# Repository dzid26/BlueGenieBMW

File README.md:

# BlueGenie BMW <br>
Bluetooth audio for BMW with CAN-bus support for steering wheel buttons control. Supported cars should be E90, E91, E92, E93, E82, E81, (also probably 5, 7-series, maybe E46).   <br> <br>

**Features**: 
- Next / Previous - (CAN-bus) steering buttons 
- OTA over Wi-Fi (hold Volume Down and Previous Song buttons on the steering to go into Dwonload mode) <br>
- Other possibilities that you can develop:
  - autmoatically enable heated seats if ambient tempreture is low)
  - display car info on your phone, if you make an app ;)
 <br>
 <br>
 
**Hardware thingies** ([BOM](https://htmlpreview.github.io/?https://github.com/dzid26/BlueGenieBMW/blob/master/Hardware/bom.html)): 
- ESP8266 - (Wemos D1 mini) ($3) (they usually come with the black sockets)  
- BK3254 (BT4.1 A2DP audio) - with UART enabled firmware (the ebay ones should be ok) ($2) 
- MCP2515 board with some transciever ($2) 
- https://oshpark.com/shared_projects/qK7vXqp4 
- Audio jack PJ-320D
- (optional) resistors (2x2.2k & 2x3.3k) for level shifting for longetivity of ESP8266. You can replace them with short wire if you're on a brave side.
<br> <br>

Solder the stuff together.
 <br> <br>

Installation: <br>
- clone the repository and also run download_libraries.bat from /lib folder  :/
- Import project to https://platformio.org/platformio-ide and flash ESP8266 using USB cable (for the first time).
- Power it with 5V cigarette charger or get Wemos power shield from ebay.
- Find K-CAN ("chasis" CAN-bus) - twisted green (CAN HIGH) and orange (CAN LOW) cables behind the radio and splice it and connect to MCP2515.  <br>

Some info regarding K-CAN - it is @100kbps  <br>
- https://us.autologic.com/news/bmw-instrument-cluster-lights-and-the-k-bus-failure  <br>
- https://www.newtis.info/tisv2/a/en/e82-123d-cou/repair-manuals/61-general-vehicle-electrical-system/2EAqiv9
- For CAN messages, refer to https://github.com/dzid26/opendbc-BMW-E8x-E9x/blob/master/bmw_e9x_e8x.dbc.

<br> <br><br> <br>
Photos:

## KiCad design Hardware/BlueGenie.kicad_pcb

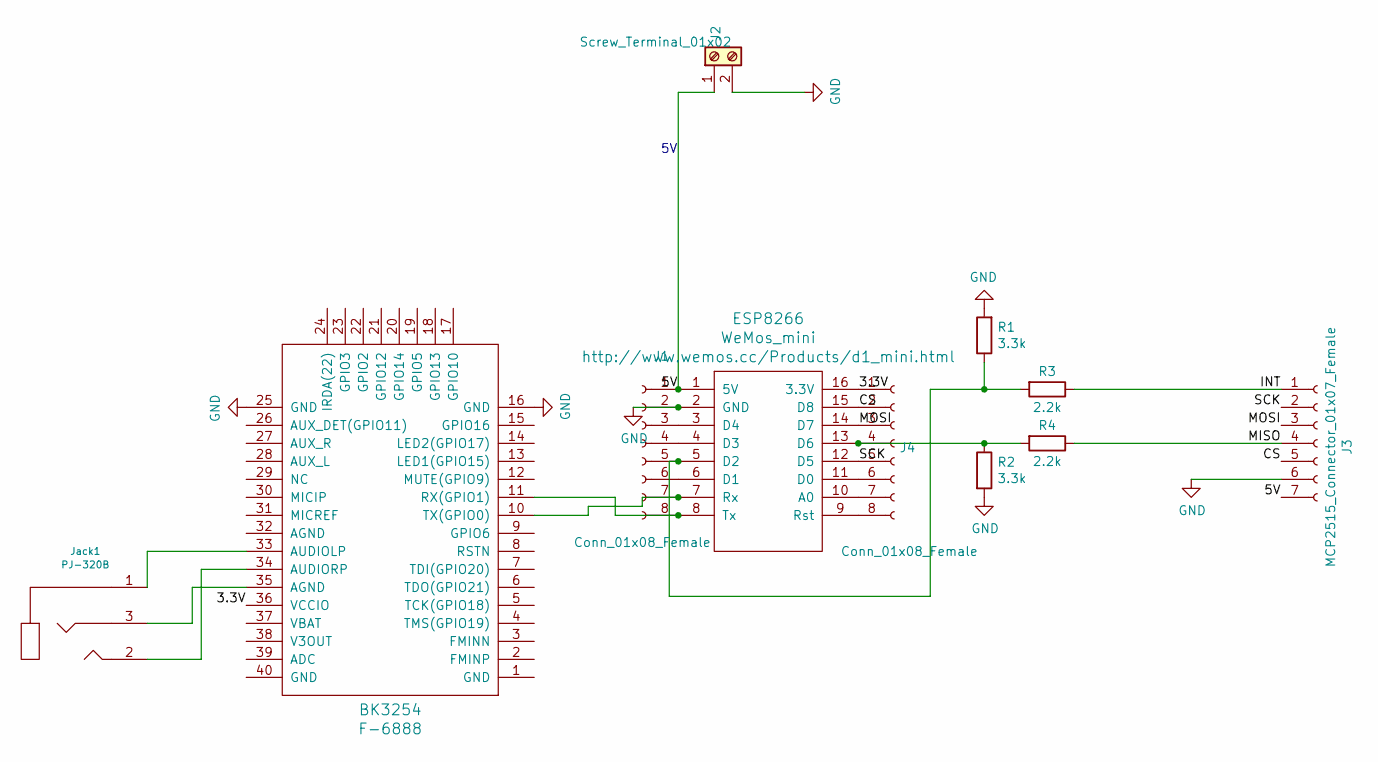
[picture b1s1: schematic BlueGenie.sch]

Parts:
BK3254: F-6888
ESP8266: WeMos_mini; D1_mini_board
J1, J4: Conn_01x08_Female; PinSocket_1x08_P2.54mm_Vertical
J2: Screw_Terminal_01x02; TerminalBlock_bornier-2_P5.08mm
J3: MCP2515_Connector_01x07_Female; PinSocket_1x07_P2.54mm_Vertical
Jack1: PJ-320B; Jack_3.5mm_PJ320D_Horizontal
R1, R2: 3.3k; R_Axial_DIN0207_L6.3mm_D2.5mm_P10.16mm_Horizontal
R3, R4: 2.2k; R_Axial_DIN0207_L6.3mm_D2.5mm_P10.16mm_Horizontal

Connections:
/3.3V: BK3254.36 (VCCIO), ESP8266.16 (3.3V), J4.1
/5V: ESP8266.1 (5V), J1.1, J2.1, J3.7
/CS: ESP8266.15 (D8), J3.5, J4.2
/INT: J3.1, R3.1
/MISO: J3.4, R4.1
/MOSI: ESP8266.14 (D7), J3.3, J4.3
/SCK: ESP8266.12 (D5), J3.2, J4.5
GND: BK3254.16 (GND), BK3254.25 (GND), ESP8266.2 (GND), J1.2, J2.2, J3.6, R1.2, R2.2
unnamed: BK3254.10 (TX(GPIO0)), ESP8266.7 (Rx), J1.7
unnamed: BK3254.11 (RX(GPIO1)), ESP8266.8 (Tx), J1.8
unnamed: BK3254.33 (AUDIOLP), Jack1.1
unnamed: BK3254.34 (AUDIORP), Jack1.2
unnamed: BK3254.35 (AGND), Jack1.3
unnamed: ESP8266.3 (D4), J1.3
unnamed: ESP8266.4 (D3), J1.4
unnamed: ESP8266.5 (D2), J1.5, R1.1, R3.2
unnamed: ESP8266.6 (D1), J1.6
unnamed: ESP8266.9 (Rst), J4.8
unnamed: ESP8266.10 (A0), J4.7
unnamed: ESP8266.11 (D0), J4.6
unnamed: ESP8266.13 (D6), J4.4, R2.1, R4.2

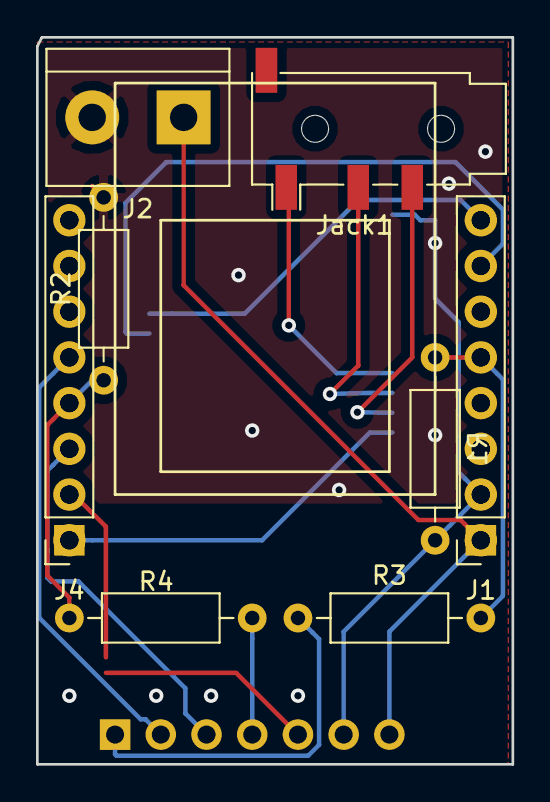
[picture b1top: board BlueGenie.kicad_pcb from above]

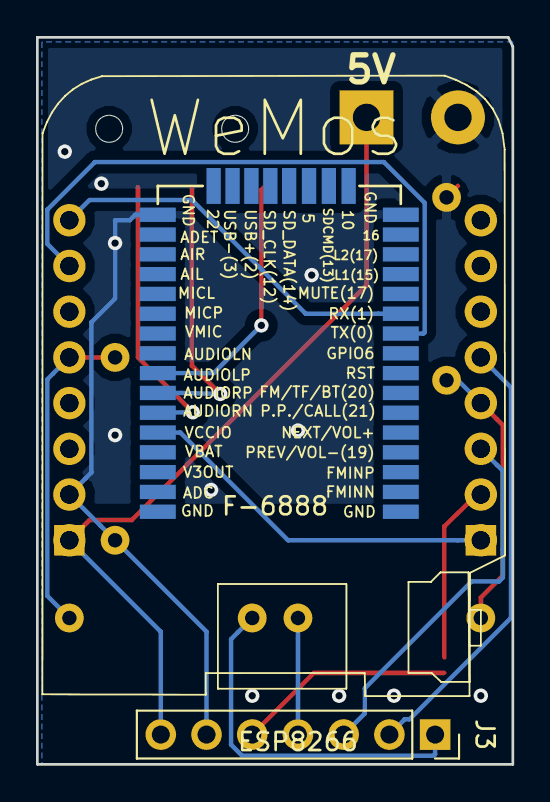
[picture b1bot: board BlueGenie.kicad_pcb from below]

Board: 2 copper layers, 26.4 x 40.4 mm, 11 parts (3 on the bottom side), 21 nets.

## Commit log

2019-02-10 Initial version. Working song skipping but draws battery in Normal mode of CAN receiver
2019-08-08 Working version.
    Issues:
    - double skip track,
    - sometimes not responding to skipping
2019-10-12 Cleaned up libraries
2019-10-12 Images of the hardware boards
2019-10-12 Photos
2019-10-12 Added GNU license back
2019-10-13 Commented out lib_dep in order to use classical folder structure and not rely on Platformio IDE for downloading libraries
2019-10-13 Added PCB KiCad project
2019-11-18 Shorted pin 12 fixed
2019-11-18 Housekeeping. Added compiler switches to differentiate from old hardware and a bench. Fixed CAN messages mask.
2020-02-15 Added photos of soldered parts. The height could be a bit smaller if soldered without headers.
2020-02-15 Added links to libraries (submodules)
2020-02-15 Updated photos
2020-02-15 Added libraries download script, because git apparently doesn't clone submodules automatically
2020-02-15 Added libraries download script,
    because git apparently doesn't clone submodules automatically
2020-02-15 Use splicer to connect to CAN network.
2020-10-27 Added cool bom
2020-10-27 Update README.md
    Link to BOM view
